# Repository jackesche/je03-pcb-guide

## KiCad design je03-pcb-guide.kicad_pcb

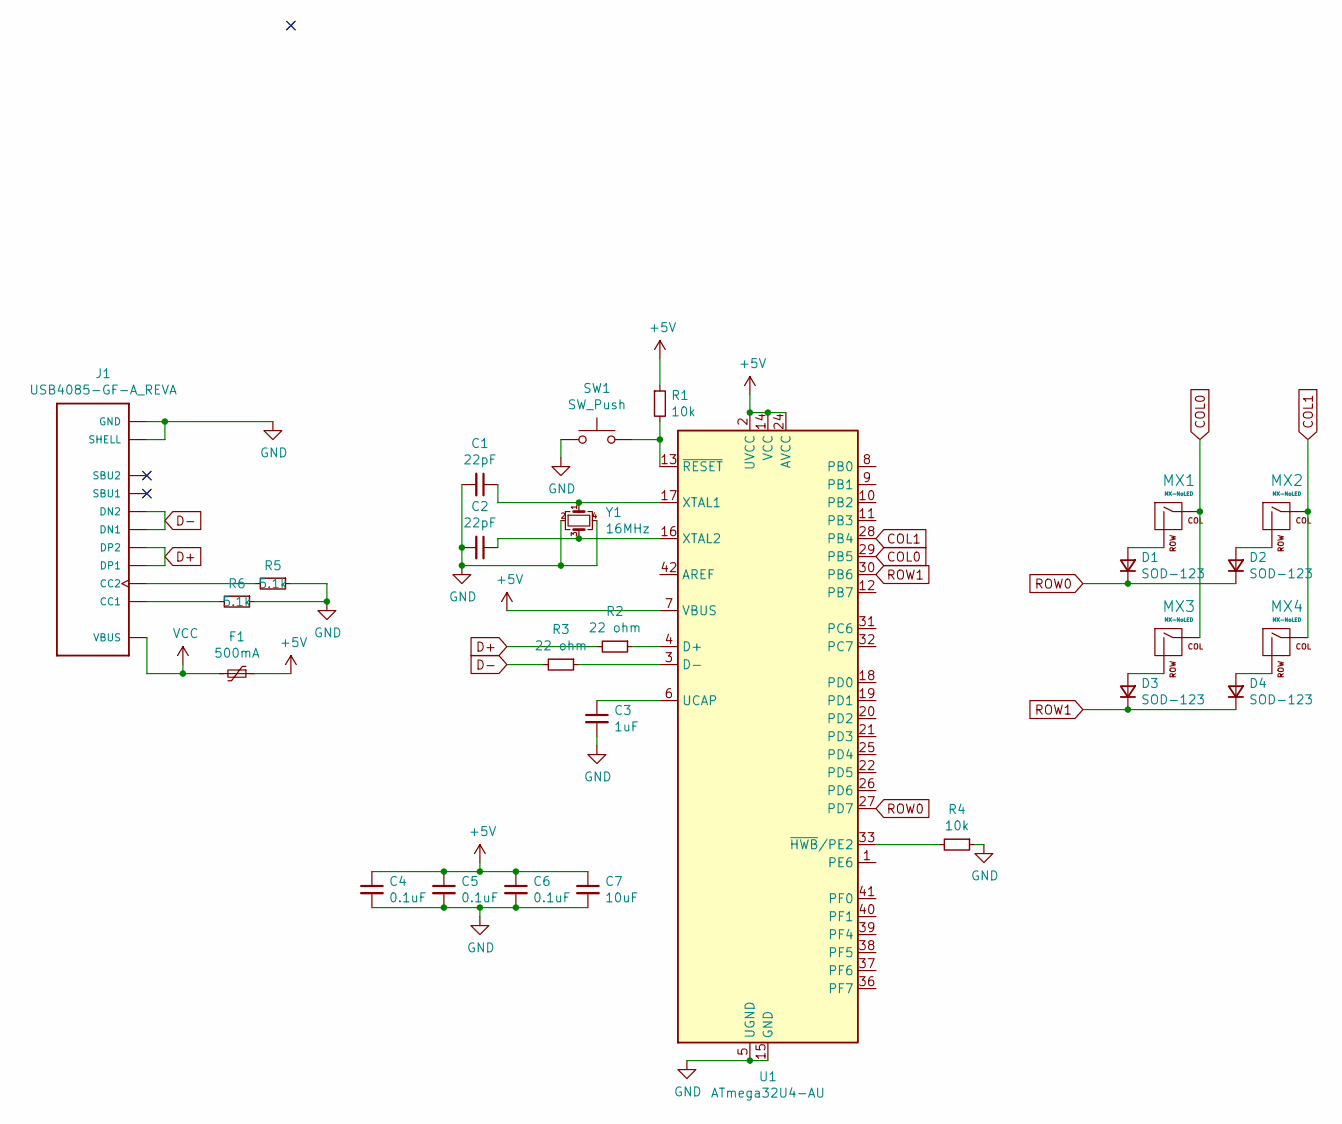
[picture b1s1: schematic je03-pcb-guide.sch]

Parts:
C1, C2: 22pF; C_0805_2012Metric
C3: 1uF; C_0805_2012Metric
C4, C5, C6: 0.1uF; C_0805_2012Metric
C7: 10uF; C_0805_2012Metric
D1, D2, D3, D4: SOD-123; D_SOD-123
F1: 500mA; Fuse_1206_3216Metric
J1: USB4085-GF-A_REVA; GCT_USB4085-GF-A_REVA
MX1, MX2, MX3, MX4: MX-NoLED; MX-1U-NoLED
R1, R4: 10k; R_0805_2012Metric
R2, R3: 22 ohm; R_0805_2012Metric
R5, R6: 5.1k; R_0603_1608Metric
SW1: SW_Push; SKQG-1155865
U1: ATmega32U4-AU; TQFP-44_10x10mm_P0.8mm
Y1: 16MHz; Crystal_SMD_3225-4Pin_3.2x2.5mm

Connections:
+5V: C4.1, C5.1, C6.1, C7.1, F1.1, R1.1, U1.2 (UVCC), U1.7 (VBUS), U1.14 (VCC), U1.24 (AVCC), U1.34 (VCC), U1.44 (AVCC)
COL0: MX1.1 (COL), MX3.1 (COL), U1.29 (PB5)
COL1: MX2.1 (COL), MX4.1 (COL), U1.28 (PB4)
D+: J1.A6 (DP1), J1.B6 (DP2), R2.2
D-: J1.A7 (DN1), J1.B7 (DN2), R3.2
GND: C1.2, C2.2, C3.2, C4.2, C5.2, C6.2, C7.2, J1.A1 (GND), J1.A12 (GND), J1.B1 (GND), J1.B12 (GND), J1.P1 (SHELL), J1.P2 (SHELL), J1.P3 (SHELL), J1.P4 (SHELL), R4.1, R5.1, R6.1, SW1.1, U1.5 (UGND), U1.15 (GND), U1.23 (GND), U1.35 (GND), U1.43 (GND), Y1.2, Y1.4
unnamed: C1.1, U1.17 (XTAL1), Y1.1
unnamed: C2.1, U1.16 (XTAL2), Y1.3
unnamed: C3.1, U1.6 (UCAP)
unnamed: D1.2 (A), MX1.2 (ROW)
unnamed: D2.2 (A), MX2.2 (ROW)
unnamed: D3.2 (A), MX3.2 (ROW)
unnamed: D4.2 (A), MX4.2 (ROW)
unnamed: J1.A5 (CC1), R6.2
unnamed: J1.B5 (CC2), R5.2
unnamed: R1.2, SW1.2, U1.13 (~RESET)
unnamed: R2.1, U1.4 (D+)
unnamed: R3.1, U1.3 (D-)
unnamed: R4.2, U1.33 (~HWB~/PE2)
ROW0: D1.1 (K), D2.1 (K), U1.27 (PD7)
ROW1: D3.1 (K), D4.1 (K), U1.30 (PB6)
VCC: F1.2, J1.A4 (VBUS), J1.A9 (VBUS), J1.B4 (VBUS), J1.B9 (VBUS)

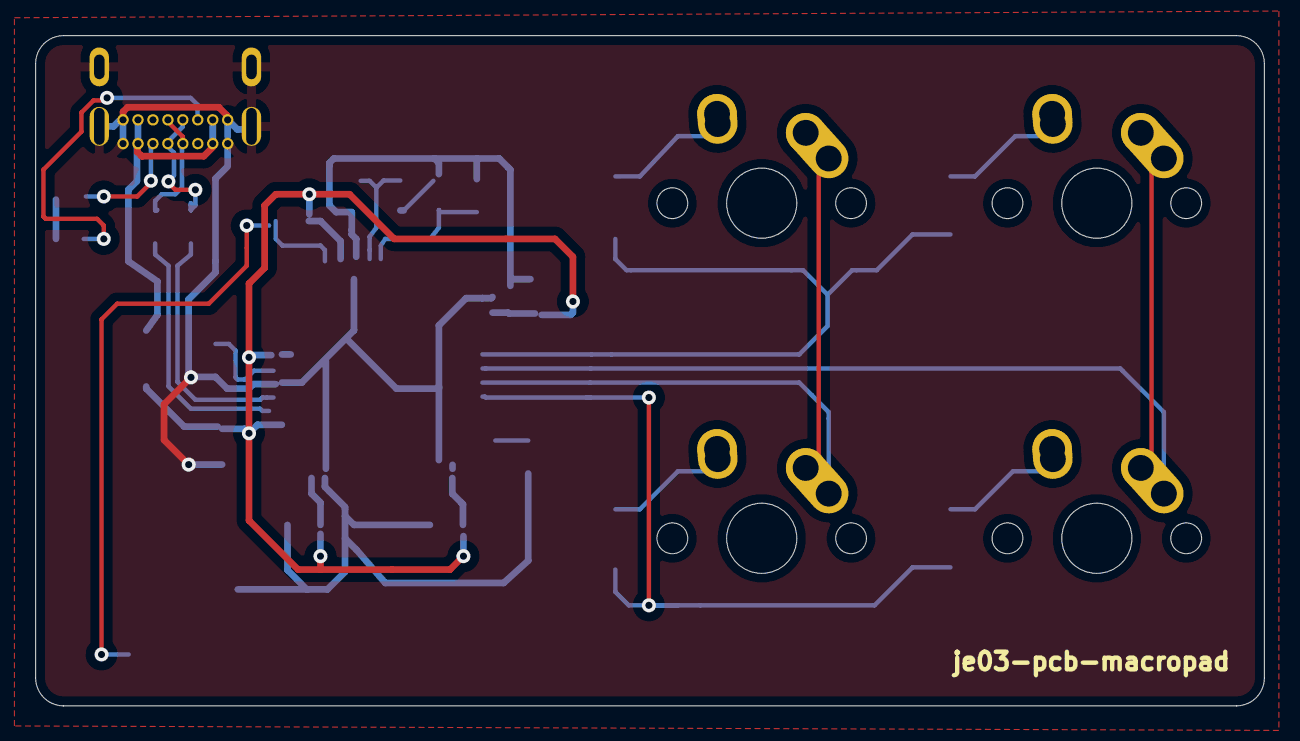
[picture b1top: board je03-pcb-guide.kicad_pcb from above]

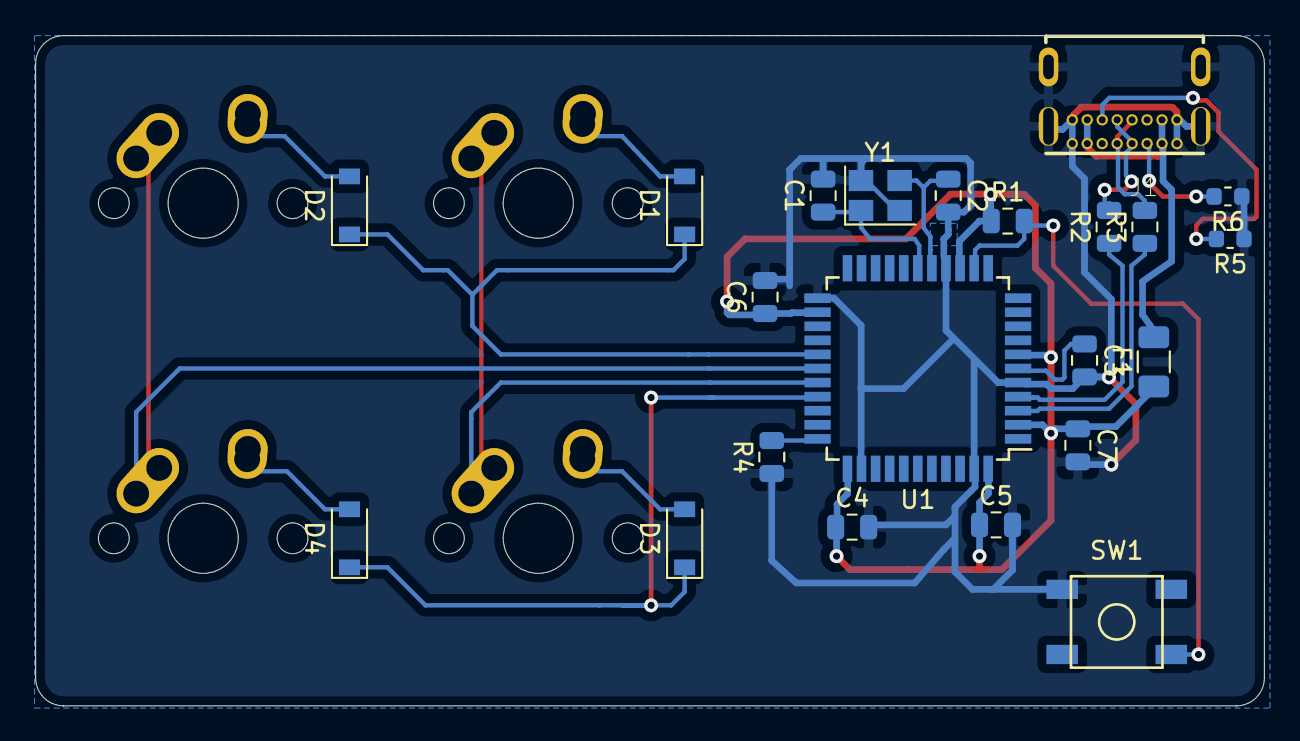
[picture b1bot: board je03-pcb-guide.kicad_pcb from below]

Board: 2 copper layers, 69.8 x 38.1 mm, 26 parts (26 on the bottom side), 22 nets.

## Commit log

2020-08-29 Project Created
    Created the project files in KiCad
2020-08-29 Add submodules
2020-08-29 Added submodules
2020-08-29 Add footprint libraries
2020-08-29 Add libraries
2020-08-29 Add components
2020-08-29 Assign components
2020-08-30 Route traces
2020-08-30 Organize file
2020-08-30 Create gerbers
2020-08-30 Add USB-C
2020-08-30 USB-C
2020-08-30 Misc
2020-08-30 Update libs
2020-11-22 Update fp-info-cache
